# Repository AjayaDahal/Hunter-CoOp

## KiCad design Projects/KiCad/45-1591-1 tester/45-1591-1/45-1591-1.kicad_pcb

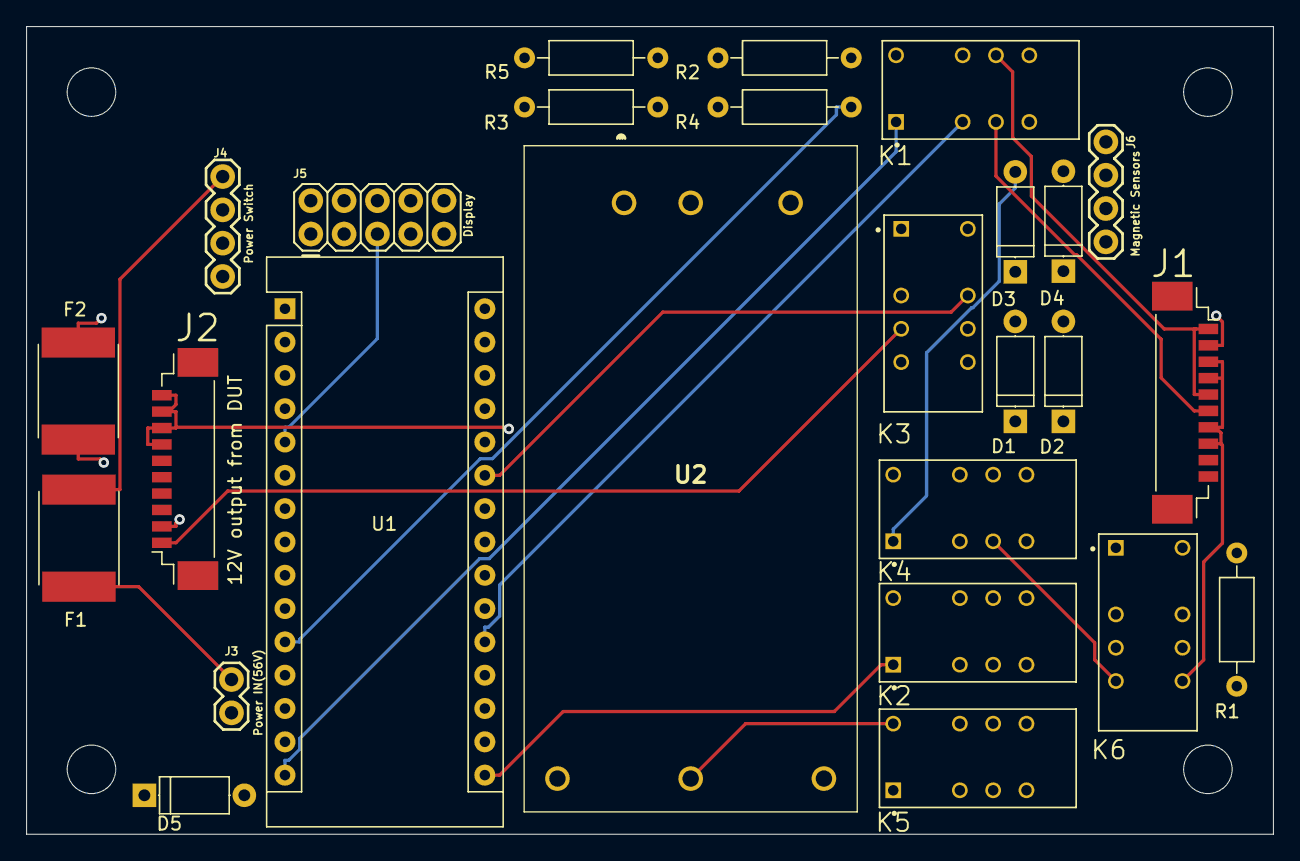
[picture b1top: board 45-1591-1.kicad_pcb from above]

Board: 4 copper layers, 95.1 x 61.6 mm, 30 parts (0 on the bottom side), 38 nets.

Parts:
D1, D2, D3, D4, D5: DIODE; D_A-405_P7.62mm_Horizontal
F1, F2: Fuse; Fuse_SMD2920
J1: 56V to the DUT; Molex_PicoBlade_53398-1071_10x1.25mm_Straight
J2: 12V output from DUT; Molex_PicoBlade_53398-1071_10x1.25mm_Straight
J3: Power IN(56V); 1X02
J4: Power Switch; 1X04
J5: Display; 2X5
J6: Magnetic Sensors; 1X04
K1, K2, K3, K4, K5, K6: EC2-5NU; RELAY_EC2-5NU
R1: 150; R_Axial_DIN0207_L6.3mm_D2.5mm_P10.16mm_Horizontal
R2: 3M; R_Axial_DIN0207_L6.3mm_D2.5mm_P10.16mm_Horizontal
R3, R4: 10k; R_Axial_DIN0207_L6.3mm_D2.5mm_P10.16mm_Horizontal
R5: 1M; R_Axial_DIN0207_L6.3mm_D2.5mm_P10.16mm_Horizontal
REF1**, REF2**, REF3**, REF4**: MountingHole_3.7mm
U1: Arduino_Nano_v3.x; Arduino_Nano
U2: RDC2072S12

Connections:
1_J1: J1.1, J1.5, K1.9
1_J2: J2.1, K3.4
2_J1: J1.2, J1.6, K1.4
2_J2: J2.2, K3.9
3_J1: J1.3, J1.4, J1.7, J1.8, K2.4, K2.9, K6.8
5V: J5.2, J6.2, J6.3, R1.2, U1.27
10_J2: J2.7, J2.8, J2.9, J2.10, K4.4, K4.9, K6.5
12V: U1.30, U2.4
12V_OUT_from_DUT: K3.5, K3.8, R2.2
56V_In: J4.3, K5.9, U2.1
56V_Out_From_Relay: F2.2, K5.8
56V_To_DUT: F2.1, K1.5, K1.8
A0: R2.1, R5.2, U1.19
A1: K1.3, U1.20
A2: K2.10, U1.21
A3: K2.3, U1.22
A4: K3.3, U1.23
A5: K4.3, U1.24
A6: K3.10, U1.25
A7: K4.10, U1.26
D0: J5.3, U1.2
D1: J5.4, U1.1
D2: J5.5, U1.5
D3: J5.6, U1.6
D4: J5.7, U1.7
D5: K5.1, U1.8
D6: D1.2, K6.1, U1.9
D7: J6.1, R3.1, U1.10
D8: J6.4, R4.2, U1.11
D9: K1.10, U1.12
D10: D2.2, K3.1, U1.13
D11: D3.2, K4.1, U1.14
D12: D4.2, K1.1, U1.15
D13: D5.2, K2.1, U1.16
GND: D1.1, D2.1, D3.1, D4.1, D5.1, J3.2, J4.1, J5.1, J5.8, J5.9, K1.12, K2.12, K3.12, K4.12, K5.12, K6.4, K6.9, K6.12, R3.2, R4.1, R5.1, U1.4, U1.29, U2.2, U2.5
unnamed: F1.1, J4.4
unnamed: F1.2, J3.1
unnamed: J4.2, R1.1

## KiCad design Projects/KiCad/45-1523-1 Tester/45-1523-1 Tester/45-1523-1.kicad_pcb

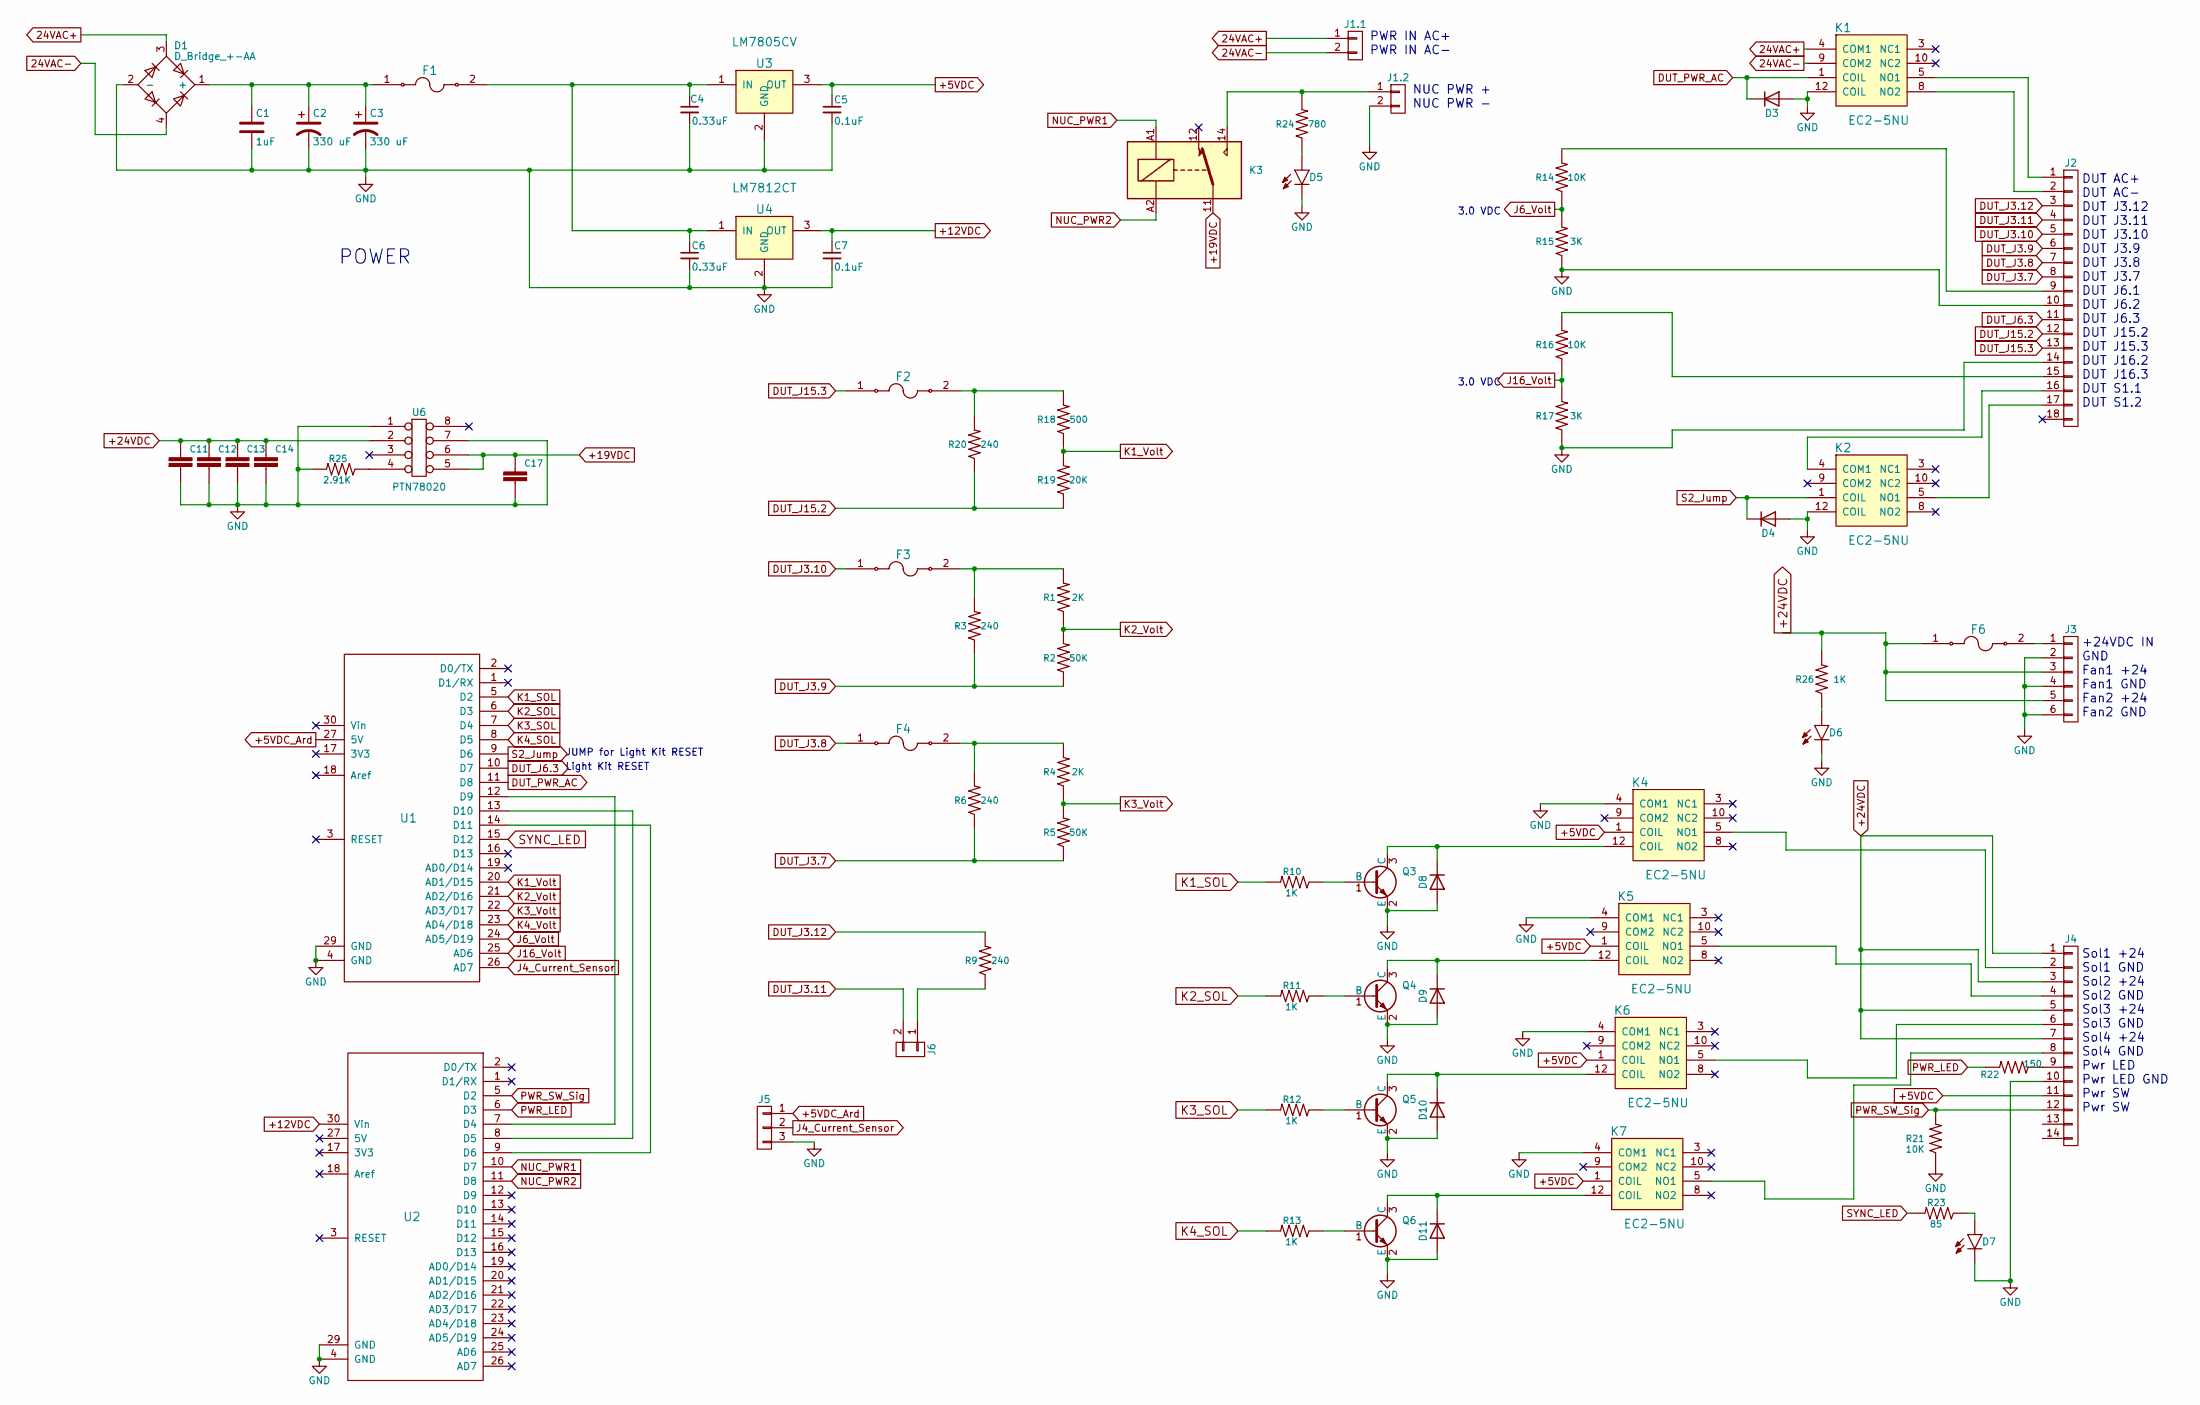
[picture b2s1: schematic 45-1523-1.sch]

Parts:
C1: 1uF; CAP-PTH-2.54
C2, C3: 330 uF; CAP-PTH-2.54
C4, C6: 0.33uF; CAP-PTH-2.54
C5, C7: 0.1uF; CAP-PTH-2.54
C11, C12, C13, C14: 4.7uF; CAP-PTH-2.54
C17: 330uF; CAP-PTH-2.54
D1: D_Bridge_+-AA; Diode_Bridge_Round_D8.9mm
D3, D4, D8, D9, D10, D11: 1N4001; D_A-405_P10.16mm_Horizontal
D5, D6, D7: LED; LED-0603
F1, F2, F3, F4, F6: 3413_0328_22; Fuse_SMD2920; MPN 3413.0328.22; Digi-Key_PN 486-1686-1-ND
J1.1, J1.2, J6: CONN_01X02; 1X02
J2: CONN_01X18; 2X10
J3: CONN_01X06; 1X06
J4: CONN_01X14; 2X8
J5: CONN_01X03; 1X03
K1, K2, K4, K5, K6, K7: EC2-5NU; Relay_EC2-5NU; MPN EC2-5NU; Digi-Key_PN 399-11052-5-ND
K3: G5Q-1; Relay_SPDT_Schrack-RT1-16A-FormC_RM5mm
Q3, Q4, Q5, Q6: BC817-40; TO-92-AMMO
R1, R4: 2K; AXIAL-0.3
R2, R5: 50K; AXIAL-0.3
R3, R6, R9, R20: 240; R_Axial_Power_L25.0mm_W6.4mm_P30.48mm
R10, R11, R12, R13, R26: 1K; AXIAL-0.3
R14, R16, R21: 10K; AXIAL-0.3
R15, R17: 3K; AXIAL-0.3
R18: 500; AXIAL-0.3
R19: 20K; AXIAL-0.3
R22: 150; AXIAL-0.3
R23: 85; AXIAL-0.3
R24: 780; AXIAL-0.3
R25: 2.91K; 0402
U1, U2: Arduino_Nano; arduino_nano
U3: LM7805CV; TO-220-3_Horizontal_Reversed; MPN L7805CV; Digi-Key_PN 497-1443-5-ND
U4: LM7812CT; TO-220-3_Horizontal_Reversed; MPN L7805CV; Digi-Key_PN 497-1443-5-ND
U6: PTN78020; PTN78020W

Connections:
24VAC+: D1.3, J1.1.1, K1.4 (COM1)
24VAC-: D1.4, J1.1.2, K1.9 (COM2)
+5VDC: C5.1, J4.11, K4.1 (COIL), K5.1 (COIL), K6.1 (COIL), K7.1 (COIL), U3.3 (OUT)
+5VDC_Ard: J5.1, U1.27 (5V)
+12VDC: C7.1, U2.30 (Vin), U4.3 (OUT)
+19VDC: C17.1, K3.11, U6.5, U6.6
+24VDC: C11.1, C12.1, C13.1, C14.1, F6.1, J3.3, J3.5, J4.1, J4.3, J4.5, J4.7, R26.P$2 (2), U6.2
DUT_J3.7: J2.8, R5.P$1 (1), R6.P$1 (1)
DUT_J3.8: F4.1, J2.7
DUT_J3.9: J2.6, R2.P$1 (1), R3.P$1 (1)
DUT_J3.10: F3.1, J2.5
DUT_J3.11: J2.4, J6.2
DUT_J3.12: J2.3, R9.P$2 (2)
DUT_J6.3: J2.11, U1.10 (D7)
DUT_J15.2: J2.12, R19.P$1 (1), R20.P$1 (1); also elsewhere on the board
DUT_J15.3: F2.1, J2.13
DUT_PWR_AC: D3.1 (K), K1.1 (COIL), U1.11 (D8)
GND: C1.2, C2.2, C3.2, C4.2, C5.2, C6.2, C7.2, C11.2, C12.2, C13.2, C14.2, C17.2, D1.2 (-), D3.2 (A), D4.2 (A), D5.C, D6.C, D7.C, D8.2 (A), D9.2 (A), D10.2 (A), D11.2 (A), J1.2.2, J2.10, J2.14, J3.2, J3.4, J3.6, J4.10, J5.3, K1.12 (COIL), K2.12 (COIL), K4.4 (COM1), K5.4 (COM1), K6.4 (COM1), K7.4 (COM1), Q3.2 (E), Q4.2 (E), Q5.2 (E), Q6.2 (E), R15.P$1 (1), R17.P$1 (1), R21.P$1 (1), R25.2, U1.4 (GND), U1.29 (GND), U2.4 (GND), U2.29 (GND), U3.2 (GND), U4.2 (GND), U6.1, U6.7
J4_Current_Sensor: J5.2, U1.26 (AD7)
J6_Volt: R14.P$1 (1), R15.P$2 (2), U1.24 (AD5/D19)
J16_Volt: R16.P$1 (1), R17.P$2 (2), U1.25 (AD6)
K1_SOL: R10.P$2 (2), U1.5 (D2)
K1_Volt: R18.P$1 (1), R19.P$2 (2), U1.20 (AD1/D15)
K2_SOL: R11.P$2 (2), U1.6 (D3)
K2_Volt: R1.P$1 (1), R2.P$2 (2), U1.21 (AD2/D16)
K3_SOL: R12.P$2 (2), U1.7 (D4)
K3_Volt: R4.P$1 (1), R5.P$2 (2), U1.22 (AD3/D17)
K4_SOL: R13.P$2 (2), U1.8 (D5)
K4_Volt: U1.23 (AD4/D18); also elsewhere on the board
NUC_PWR1: K3.A1, U2.10 (D7)
NUC_PWR2: K3.A2, U2.11 (D8)
unnamed: C1.1, C2.1, C3.1, D1.1 (+), F1.1
unnamed: C4.1, C6.1, F1.2, U3.1 (IN), U4.1 (IN)
unnamed: D5.A, R24.P$1 (1)
unnamed: D6.A, R26.P$1 (1)
unnamed: D7.A, R23.P$1 (1)
unnamed: D8.1 (K), K4.12 (COIL), Q3.3 (C)
unnamed: D9.1 (K), K5.12 (COIL), Q4.3 (C)
unnamed: D10.1 (K), K6.12 (COIL), Q5.3 (C)
unnamed: D11.1 (K), K7.12 (COIL), Q6.3 (C)
unnamed: F2.2, R18.P$2 (2), R20.P$2 (2)
unnamed: F3.2, R1.P$2 (2), R3.P$2 (2)
unnamed: F4.2, R4.P$2 (2), R6.P$2 (2)
unnamed: F6.2, J3.1
unnamed: J1.2.1, K3.14, R24.P$2 (2)
unnamed: J2.1, K1.5 (NO1)
unnamed: J2.2, K1.8 (NO2)
unnamed: J2.9, R14.P$2 (2)
unnamed: J2.15, R16.P$2 (2)
unnamed: J2.16, K2.4 (COM1)
unnamed: J2.17, K2.5 (NO1)
unnamed: J4.2, K4.5 (NO1)
unnamed: J4.4, K5.5 (NO1)
unnamed: J4.6, K6.5 (NO1)
unnamed: J4.8, K7.5 (NO1)
unnamed: J4.9, R22.P$1 (1)
unnamed: J6.1, R9.P$1 (1)
unnamed: Q3.1 (B), R10.P$1 (1)
unnamed: Q4.1 (B), R11.P$1 (1)
unnamed: Q5.1 (B), R12.P$1 (1)
unnamed: Q6.1 (B), R13.P$1 (1)
unnamed: R25.1, U6.4
unnamed: U1.12 (D9), U2.7 (D4)
unnamed: U1.13 (D10), U2.8 (D5)
unnamed: U1.14 (D11), U2.9 (D6)
PWR_LED: R22.P$2 (2), U2.6 (D3)
PWR_SW_Sig: J4.12, R21.P$2 (2), U2.5 (D2)
S2_Jump: D4.1 (K), K2.1 (COIL), U1.9 (D6)
SYNC_LED: R23.P$2 (2), U1.15 (D12)

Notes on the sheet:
Light Kit RESET
JUMP for Light Kit RESET
3.0 VDC
Sol1 +24 Sol1 GND Sol2 +24 Sol2 GND Sol3 +24 Sol3 GND Sol4 +24 Sol4 GND Pwr LED Pwr LED GND Pwr SW Pwr SW
DUT AC+ DUT AC- DUT J3.12 DUT J3.11 DUT J3.10 DUT J3.9 DUT J3.8 DUT J3.7 DUT J6.1 DUT J6.2 DUT J6.3 DUT J15.2 DUT J15.3 DUT J16.2 DUT J16.3 DUT S1.1 DUT S1.2
PWR IN AC+ PWR IN AC-
POWER
+24VDC IN GND Fan1 +24 Fan1 GND Fan2 +24 Fan2 GND
NUC PWR + NUC PWR -

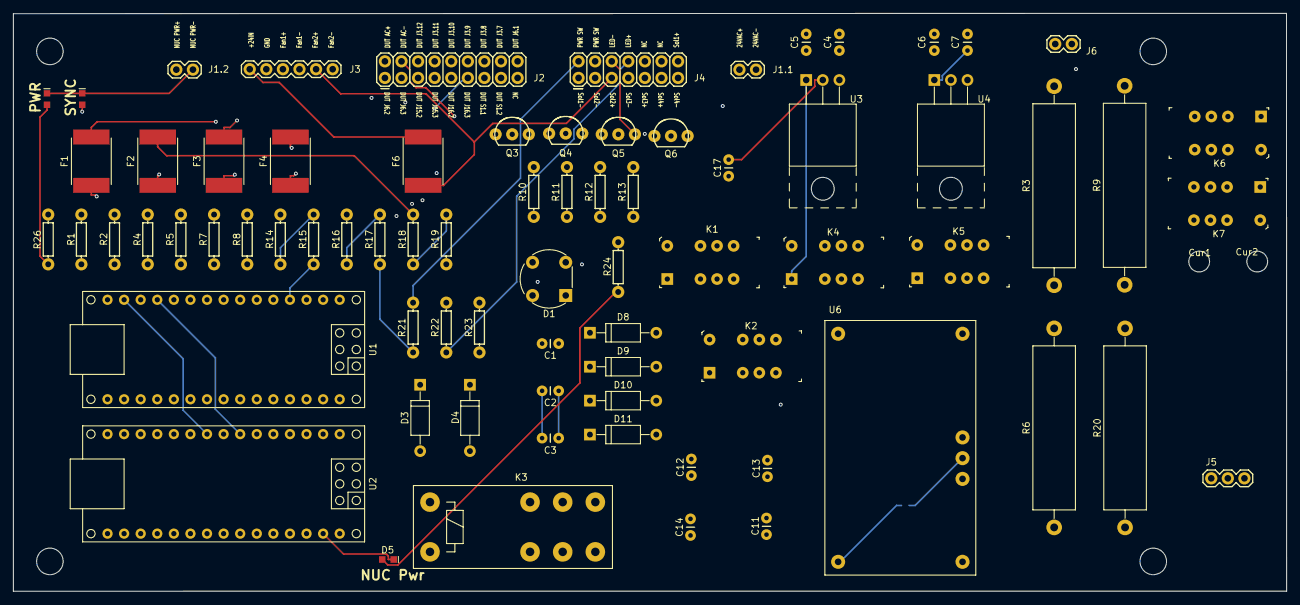
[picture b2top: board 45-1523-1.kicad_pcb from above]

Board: 4 copper layers, 195.0 x 88.5 mm, 82 parts (1 on the bottom side), 69 nets.

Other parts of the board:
Cur1, Cur2: MountingHole_5mm
M1, M2, M3, M4: MountingHole_3mm
R7: 2K; AXIAL-0.3
R8: 50K; AXIAL-0.3

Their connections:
DUT_J15.2: R8.P$1; also elsewhere on the board
K4_Volt: R7.P$1, R8.P$2; also elsewhere on the board

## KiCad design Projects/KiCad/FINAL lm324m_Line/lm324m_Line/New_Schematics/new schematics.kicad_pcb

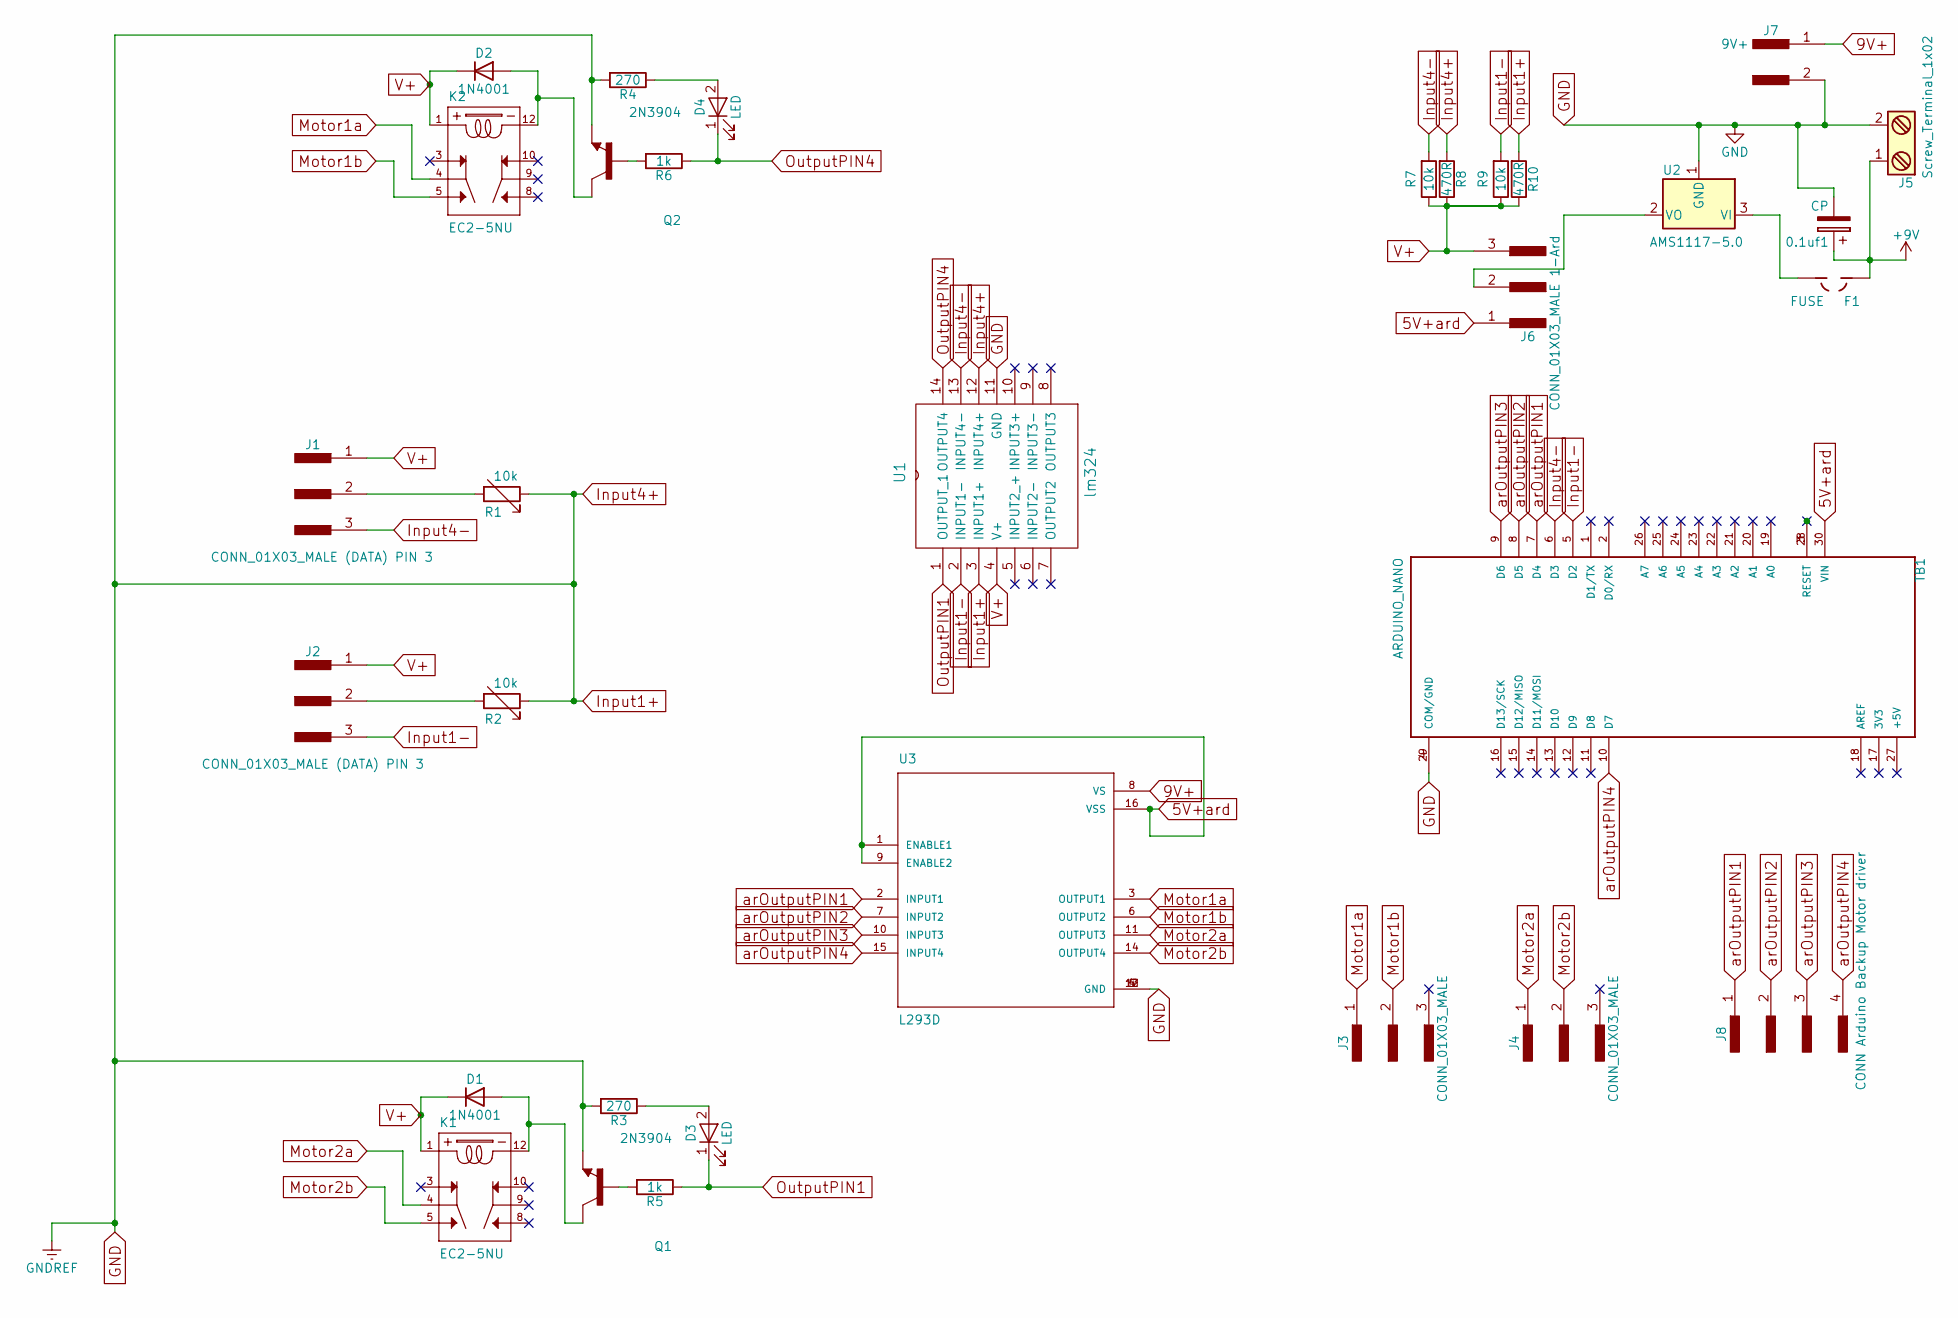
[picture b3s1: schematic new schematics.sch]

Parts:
0.1uf1: CP; CP_Radial_D4.0mm_P1.50mm
D1, D2: 1N4001; D_DO-15_P15.24mm_Horizontal
D3, D4: LED; LED_D4.0mm
F1: FUSE; C320C
J1, J2: CONN_01X03_MALE (DATA) PIN 3; PinHeader_1x03_P2.54mm_Vertical
J3, J4: CONN_01X03_MALE; PinHeader_1x03_P2.54mm_Vertical
J5: Screw_Terminal_1x02; PinHeader_1x02_P2.54mm_Vertical
J6: CONN_01X03_MALE 1-Ard; PinHeader_1x03_P2.54mm_Vertical
J7: 9V+; PinHeader_1x02_P2.54mm_Vertical
J8: CONN Arduino Backup Motor driver; PinHeader_1x04_P2.54mm_Vertical
K1, K2: EC2-5NU; RELAY_EC2-5NU
Q1, Q2: 2N3904; TO-92_Inline_Wide
R1, R2: 10k; Potentiometer_Trimmer_ACP_CA6v_Horizontal
R3, R4: 270; R_Axial_DIN0309_L9.0mm_D3.2mm_P20.32mm_Horizontal
R5, R6: 1k; R_Axial_DIN0309_L9.0mm_D3.2mm_P20.32mm_Horizontal
R7, R9: 10k; R_Axial_DIN0309_L9.0mm_D3.2mm_P20.32mm_Horizontal
R8, R10: 470R; R_Axial_DIN0309_L9.0mm_D3.2mm_P20.32mm_Horizontal
TB1: ARDUINO_NANO; SHIELD_ARDUINO_NANO
U1: lm324; LM324N
U2: AMS1117-5.0; TO-126_Vertical
U3: L293D; DIP880W50P254L2000H510Q16

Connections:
5V+ard: J6.1, TB1.30 (VIN), U3.1 (ENABLE1), U3.9 (ENABLE2), U3.16 (VSS)
9V+: J7.1, U3.8 (VS)
+9V: 0.1uf1.1, F1.1, J5.1
GND: 0.1uf1.2, J5.2, J7.2, Q1.1 (E), Q2.1 (E), R1.1, R2.1, R3.2, R4.2, R8.2, R10.2, TB1.4 (COM/GND), TB1.29 (COM/GND), U1.3 (INPUT1+), U1.11 (GND), U1.12 (INPUT4+), U2.1 (GND), U3.4 (GND), U3.5 (GND), U3.12 (GND), U3.13 (GND)
Input1-: J2.3, R9.2, TB1.5 (D2), U1.2 (INPUT1-)
Input4-: J1.3, R7.2, TB1.6 (D3), U1.13 (INPUT4-)
Motor1a: J3.1, K2.4, U3.3 (OUTPUT1)
Motor1b: J3.2, K2.5, U3.6 (OUTPUT2)
Motor2a: J4.1, K1.4, U3.11 (OUTPUT3)
Motor2b: J4.2, K1.5, U3.14 (OUTPUT4)
unnamed: D1.2 (A), K1.12, Q1.3 (C)
unnamed: D2.2 (A), K2.12, Q2.3 (C)
unnamed: D3.2 (A), R3.1
unnamed: D4.2 (A), R4.1
unnamed: F1.2, U2.3 (VI)
unnamed: J1.2, R1.2
unnamed: J2.2, R2.2
unnamed: J6.2, U2.2 (VO)
unnamed: Q1.2 (B), R5.2
unnamed: Q2.2 (B), R6.2
unnamed: TB1.3 (RESET), TB1.28 (RESET)
OutputPIN1: D3.1 (K), R5.1, U1.1 (OUTPUT_1)
OutputPIN4: D4.1 (K), R6.1, U1.14 (OUTPUT4)
V+: D1.1 (K), D2.1 (K), J1.1, J2.1, J6.3, K1.1, K2.1, R7.1, R8.1, R9.1, R10.1, U1.4 (V+)
arOutputPIN1: J8.1, TB1.7 (D4), U3.2 (INPUT1)
arOutputPIN2: J8.2, TB1.8 (D5), U3.7 (INPUT2)
arOutputPIN3: J8.3, TB1.9 (D6), U3.10 (INPUT3)
arOutputPIN4: J8.4, TB1.10 (D7), U3.15 (INPUT4)

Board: 2 copper layers, 32 parts (0 on the bottom side), 28 nets, no tracks yet.

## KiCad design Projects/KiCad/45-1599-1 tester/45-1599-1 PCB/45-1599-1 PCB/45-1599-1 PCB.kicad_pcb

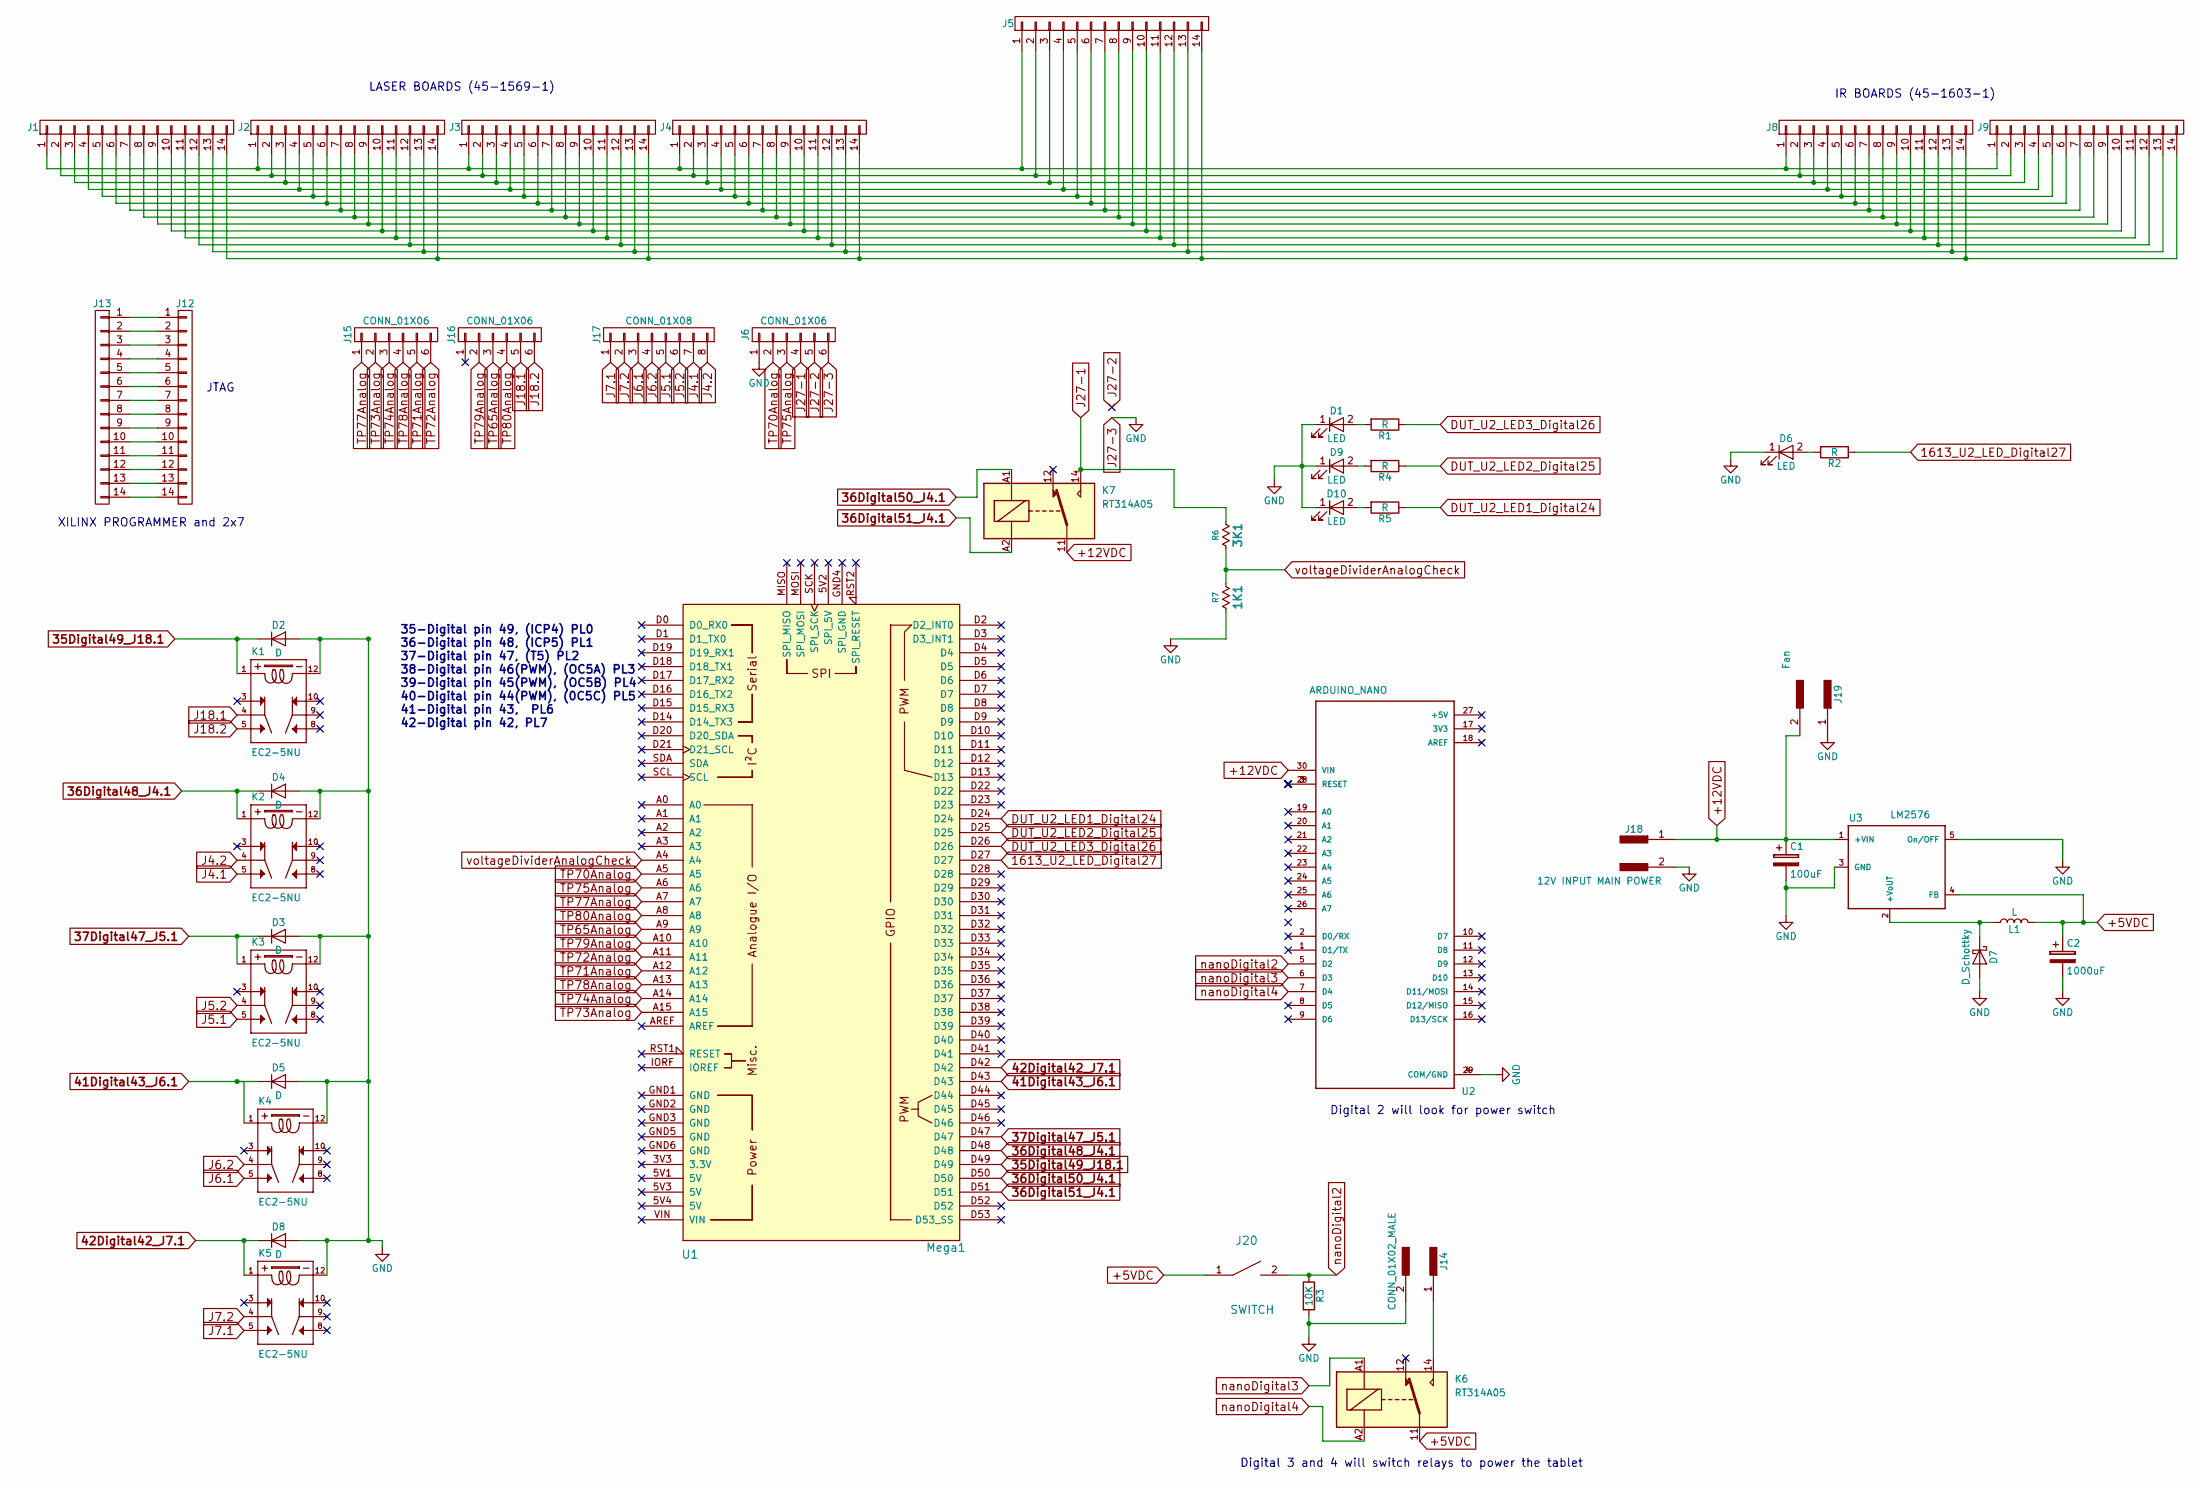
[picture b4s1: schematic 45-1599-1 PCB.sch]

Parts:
1K1: R7; R_Axial_DIN0207_L6.3mm_D2.5mm_P15.24mm_Horizontal
3K1: R6; R_Axial_DIN0207_L6.3mm_D2.5mm_P15.24mm_Horizontal
C1: 100uF; CP_Radial_D6.3mm_P2.50mm
C2: 1000uF; CP_Radial_D6.3mm_P2.50mm
D1, D6, D9, D10: LED; LED_D5.0mm_FlatTop
D2, D3, D4, D5, D8: D; D_A-405_P10.16mm_Horizontal
D7: D_Schottky; D_5W_P10.16mm_Horizontal
J1, J2, J3, J4, J5, J8, J9, J12: CONN_01X14; 2X8
J6, J15, J16: CONN_01X06; 2X8
J13: CONN_01X14; PinSocket_2x07_P2.00mm_Vertical_SMD
J14: CONN_01X02_MALE; PinHeader_1x02_P2.00mm_Vertical
J17: CONN_01X08; 2X8
J18: 12V INPUT MAIN POWER; PinSocket_1x02_P2.54mm_Vertical
J19: Fan; PinSocket_1x02_P2.54mm_Vertical
J20: SWITCH; PinSocket_1x02_P2.54mm_Vertical
K1, K2, K3, K4, K5: EC2-5NU; RELAY_EC2-5NU
K6, K7: RT314A05; Relay_SPDT_Schrack-RT1-16A-FormC_RM5mm
L1: L; L_Axial_L5.3mm_D2.2mm_P2.54mm_Vertical_Vishay_IM-1
Mega1: U1; Arduino_Mega2560_Shield
R1, R2, R4, R5: R; R_Axial_DIN0207_L6.3mm_D2.5mm_P15.24mm_Horizontal
R3: 10K; R_Axial_DIN0207_L6.3mm_D2.5mm_P15.24mm_Horizontal
U2: ARDUINO_NANO; SHIELD_ARDUINO_NANO
U3: LM2576; TO-220-5_Horizontal

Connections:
35Digital49_J18.1: D2.1 (K), K1.1, Mega1.D49
36Digital48_J4.1: D4.1 (K), K2.1, Mega1.D48
36Digital50_J4.1: K7.A1, Mega1.D50
36Digital51_J4.1: K7.A2, Mega1.D51
37Digital47_J5.1: D3.1 (K), K3.1, Mega1.D47
41Digital43_J6.1: D5.1 (K), K4.1, Mega1.D43
42Digital42_J7.1: D8.1 (K), K5.1, Mega1.D42
1613_U2_LED_Digital27: Mega1.D27, R2.1
+5VDC: C2.1, J20.1, K6.11, L1.2, U3.4 (FB)
+12VDC: C1.1, J18.1, J19.2, K7.11, U2.30 (VIN), U3.1 (+VIN)
DUT_U2_LED1_Digital24: Mega1.D24, R5.1
DUT_U2_LED2_Digital25: Mega1.D25, R4.1
DUT_U2_LED3_Digital26: Mega1.D26, R1.1
J4.1: J17.7, K2.5
J4.2: J17.8, K2.4
J5.1: J17.5, K3.5
J5.2: J17.6, K3.4
J6.1: J17.3, K4.5
J6.2: J17.4, K4.4
J7.1: J17.1, K5.5
J7.2: J17.2, K5.4
J18.1: J16.5, K1.4
J18.2: J16.6, K1.5
J27-1: 3K1.1, J6.4, K7.14; also elsewhere on the board
J27-3: 1K1.2, C1.2, C2.2, D1.1 (K), D2.2 (A), D3.2 (A), D4.2 (A), D5.2 (A), D6.1 (K), D7.2 (A), D8.2 (A), D9.1 (K), D10.1 (K), J6.1, J6.6, J14.2, J18.2, J19.1, K1.12, K2.12, K3.12, K4.12, K5.12, R3.2, U2.4 (COM/GND), U2.29 (COM/GND), U3.3 (GND), U3.5 (On/OFF); also elsewhere on the board
unnamed: D1.2 (A), R1.2
unnamed: D6.2 (A), R2.2
unnamed: D7.1 (K), L1.1, U3.2 (+VoUT)
unnamed: D9.2 (A), R4.2
unnamed: D10.2 (A), R5.2
unnamed: J1.1, J2.1, J3.1, J4.1, J5.1, J8.1, J9.1
unnamed: J1.2, J2.2, J3.2, J4.2, J5.2, J8.2, J9.2
unnamed: J1.3, J2.3, J3.3, J4.3, J5.3, J8.3, J9.3
unnamed: J1.4, J2.4, J3.4, J4.4, J5.4, J8.4, J9.4
unnamed: J1.5, J2.5, J3.5, J4.5, J5.5, J8.5, J9.5
unnamed: J1.6, J2.6, J3.6, J4.6, J5.6, J8.6, J9.6
unnamed: J1.7, J2.7, J3.7, J4.7, J5.7, J8.7, J9.7
unnamed: J1.8, J2.8, J3.8, J4.8, J5.8, J8.8, J9.8
unnamed: J1.9, J2.9, J3.9, J4.9, J5.9, J8.9, J9.9
unnamed: J1.10, J2.10, J3.10, J4.10, J5.10, J8.10, J9.10
unnamed: J1.11, J2.11, J3.11, J4.11, J5.11, J8.11, J9.11
unnamed: J1.12, J2.12, J3.12, J4.12, J5.12, J8.12, J9.12
unnamed: J1.13, J2.13, J3.13, J4.13, J5.13, J8.13, J9.13
unnamed: J1.14, J2.14, J3.14, J4.14, J5.14, J8.14, J9.14
unnamed: J12.1, J13.1
unnamed: J12.2, J13.2
unnamed: J12.3, J13.3
unnamed: J12.4, J13.4
unnamed: J12.5, J13.5
unnamed: J12.6, J13.6
unnamed: J12.7, J13.7
unnamed: J12.8, J13.8
unnamed: J12.9, J13.9
unnamed: J12.10, J13.10
unnamed: J12.11, J13.11
unnamed: J12.12, J13.12
unnamed: J12.13, J13.13
unnamed: J12.14, J13.14
unnamed: J14.1, K6.14
unnamed: U2.3 (RESET), U2.28 (RESET)
TP65Analog: J16.3, Mega1.A9
TP70Analog: J6.2, Mega1.A5
TP71Analog: J15.5, Mega1.A12
TP72Analog: J15.6, Mega1.A11
TP73Analog: J15.2, Mega1.A15
TP74Analog: J15.3, Mega1.A14
TP75Analog: J6.3, Mega1.A6
TP77Analog: J15.1, Mega1.A7
TP78Analog: J15.4, Mega1.A13
TP79Analog: J16.2, Mega1.A10
TP80Analog: J16.4, Mega1.A8
nanoDigital2: J20.2, R3.1, U2.5 (D2)
nanoDigital3: K6.A1, U2.6 (D3)
nanoDigital4: K6.A2, U2.7 (D4)
voltagDividerAnalogCheck: 1K1.1, 3K1.2, Mega1.A4; also elsewhere on the board

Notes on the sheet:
LASER BOARDS (45-1569-1)
JTAG
Digital 2 will look for power switch
Digital 3 and 4 will switch relays to power the tablet
XILINX PROGRAMMER and 2x7
35-Digital pin 49, (ICP4) PL0 36-Digital pin 48, (ICP5) PL1 37-Digital pin 47, (T5) PL2 38-Digital pin 46(PWM), (OC5A) PL3 39-Digital pin 45(PWM), (OC5B) PL4 40-Digital pin 44(PWM), (0C5C) PL5 41-Digital pin 43, PL6 42-Digital pin 42, PL7
IR BOARDS (45-1603-1)

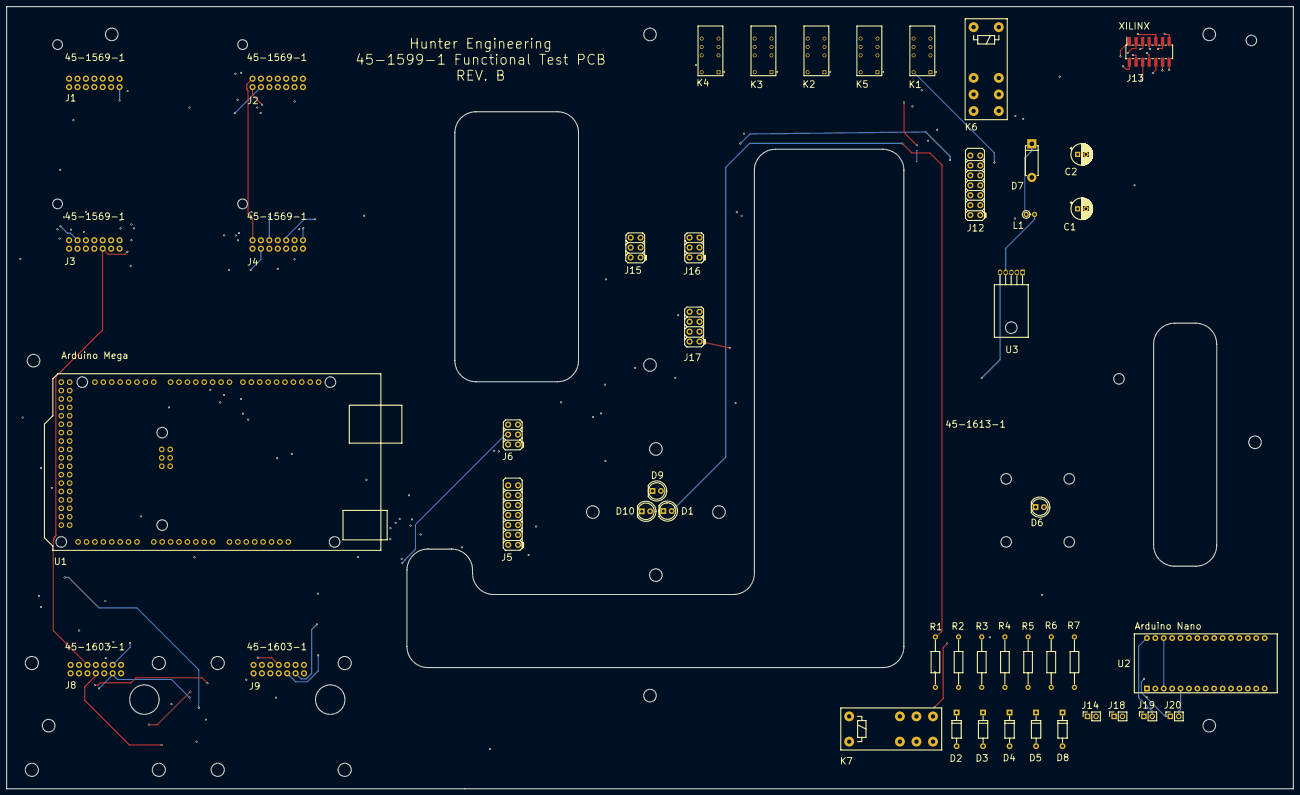
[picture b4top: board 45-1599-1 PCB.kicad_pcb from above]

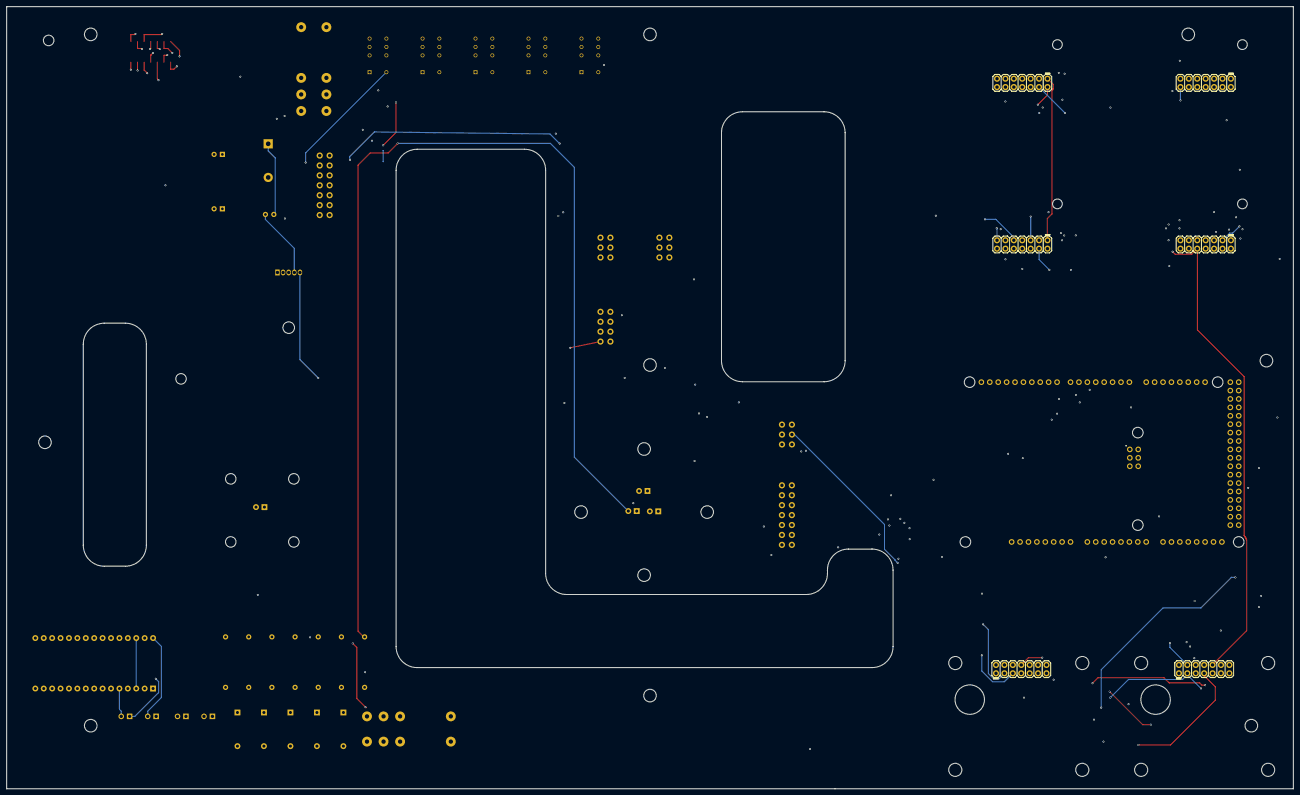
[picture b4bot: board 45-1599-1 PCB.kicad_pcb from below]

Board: 4 copper layers, 388.6 x 236.2 mm, 47 parts (7 on the bottom side), 75 nets.

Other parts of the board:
R6: R6; R_Axial_DIN0207_L6.3mm_D2.5mm_P15.24mm_Horizontal
R7: R7; R_Axial_DIN0207_L6.3mm_D2.5mm_P15.24mm_Horizontal

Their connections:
J27-1: R6.1; also elsewhere on the board
J27-3: R7.2; also elsewhere on the board
voltagDividerAnalogCheck: R6.2, R7.1; also elsewhere on the board
